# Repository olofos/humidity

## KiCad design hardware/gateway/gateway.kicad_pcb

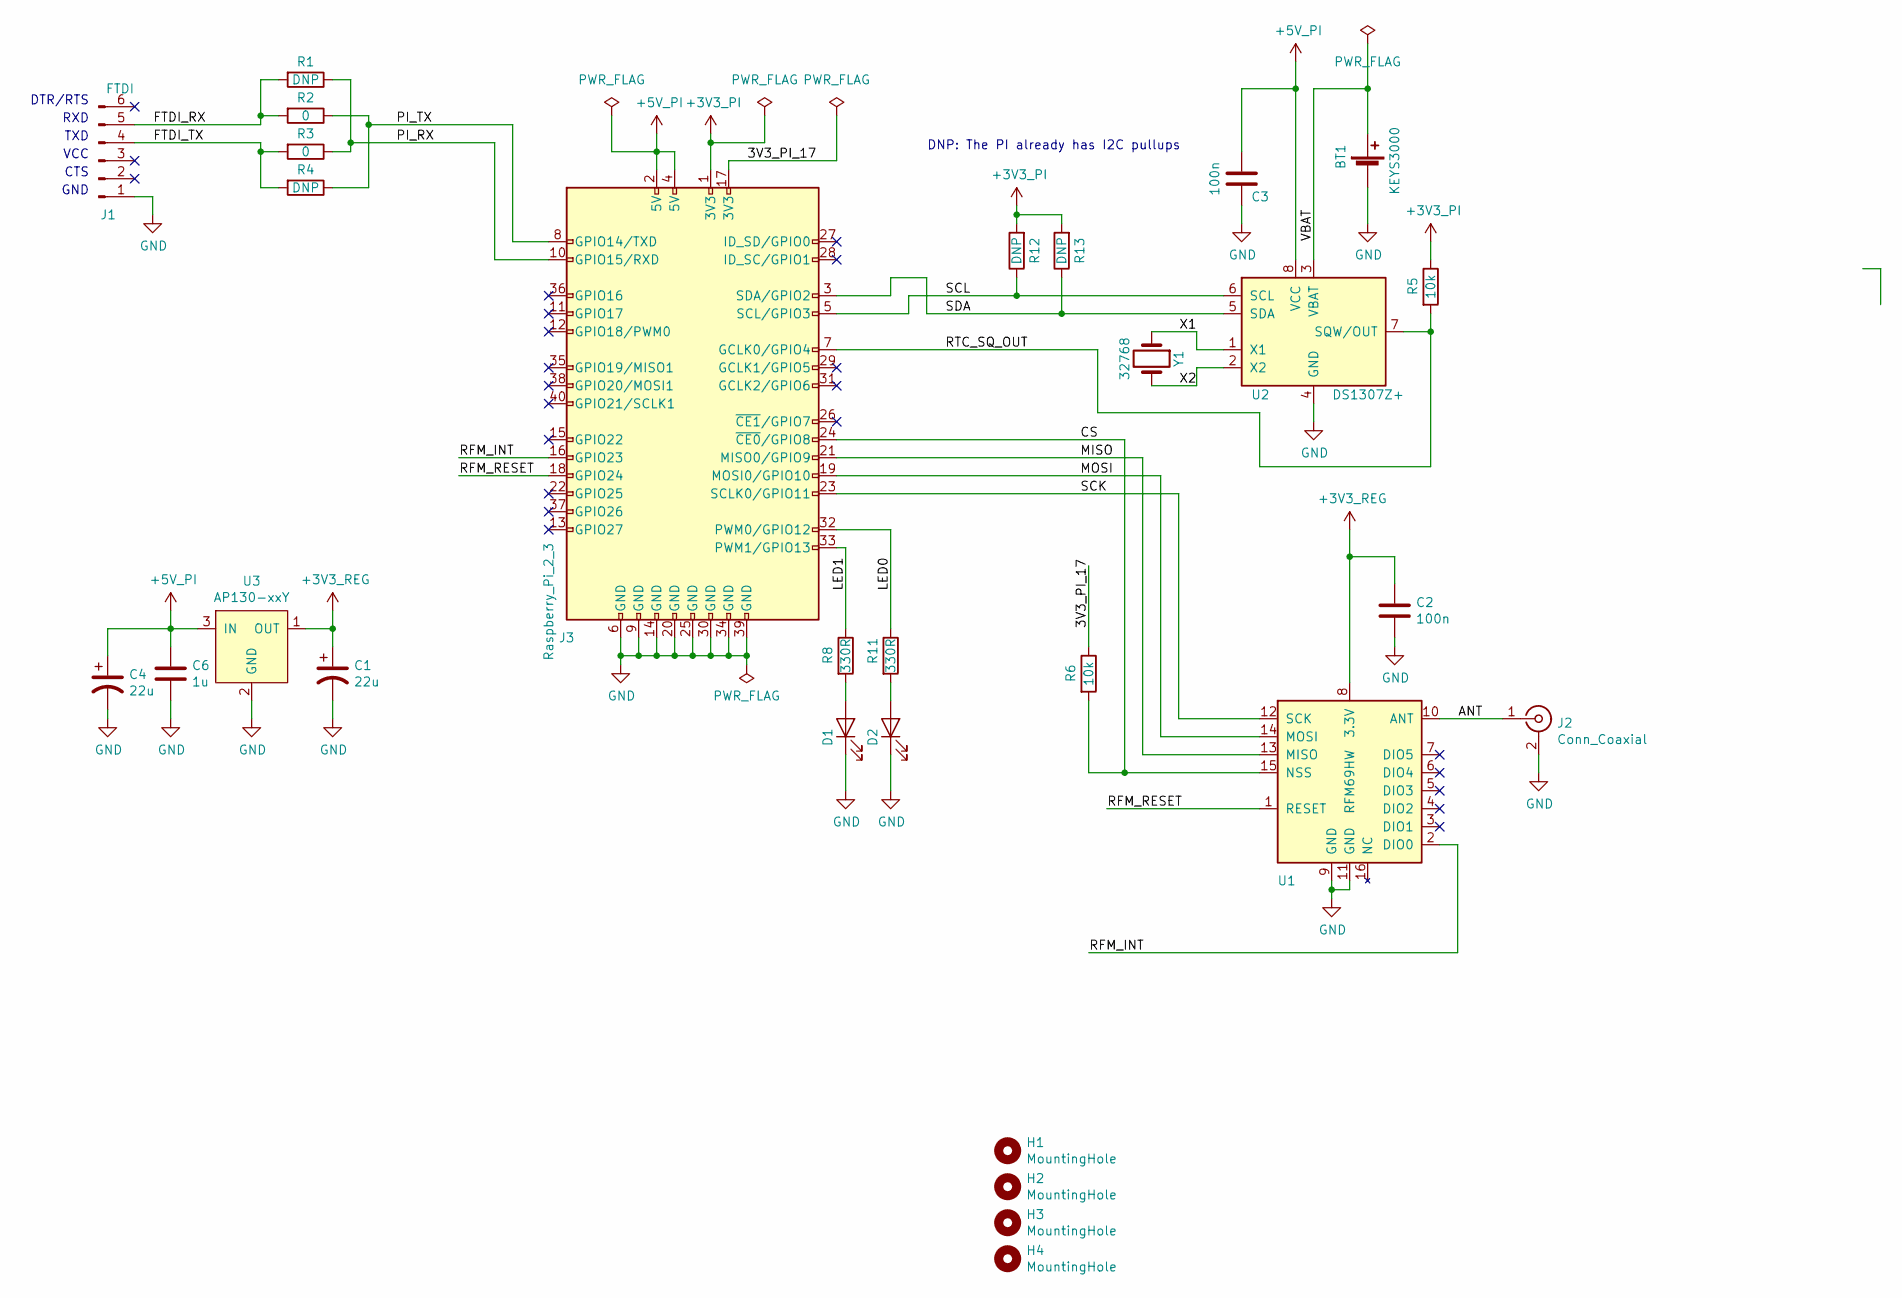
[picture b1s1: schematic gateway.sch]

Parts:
BT1: KEYS3000; CR1216_Keystone_3000
C1, C4: 22u; CP_Elec_5x5.3
C2, C3: 100n; C_0603_1608Metric_Pad1.05x0.95mm_HandSolder
C6: 1u; C_0805_2012Metric_Pad1.15x1.40mm_HandSolder
D1: KP-2012LSURCK; LED_0805_2012Metric_Pad1.15x1.40mm_HandSolder
D2: KP-2012LSGC; LED_0805_2012Metric_Pad1.15x1.40mm_HandSolder
H1, H2, H3, H4: MountingHole; MountingHole_2.7mm_M2.5
J1: FTDI; PinHeader_1x06_P2.54mm_Horizontal
J2: Conn_Coaxial; Adam_Tech_SMA_Female_RF2-19A
J3: Raspberry_Pi_2_3; PinSocket_2x20_P2.54mm_Vertical_SMD
R1, R4, R12, R13: DNP; R_0603_1608Metric_Pad1.05x0.95mm_HandSolder-DNP
R2, R3: 0; R_0603_1608Metric_Pad1.05x0.95mm_HandSolder
R5, R6: 10k; R_0603_1608Metric_Pad1.05x0.95mm_HandSolder
R8, R11: 330R; R_0603_1608Metric_Pad1.05x0.95mm_HandSolder
U1: RFM69HW
U2: DS1307Z+; SOIC-8_3.9x4.9mm_P1.27mm
U3: AP130-xxY; SOT-89-3_Handsoldering
Y1: 32768; Crystal_C26-LF_D2.1mm_L6.5mm_Horizontal

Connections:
+3V3_PI: J3.1 (3V3), R5.1, R12.2, R13.2
+3V3_REG: C1.1, C2.1, U1.8 (3.3V), U3.1 (OUT)
+5V_PI: C3.1, C4.1, C6.1, J3.2 (5V), J3.4 (5V), U2.8 (VCC), U3.3 (IN)
/3V3_PI_17: J3.17 (3V3), R6.1
/ANT: J2.1 (In), U1.10 (ANT)
/CS: J3.24 (~CE0~/GPIO8), R6.2, U1.15 (NSS)
/FTDI_RX: J1.5, R1.2, R2.2
/FTDI_TX: J1.4, R3.2, R4.2
/LED0: J3.32 (PWM0/GPIO12), R11.1
/LED1: J3.33 (PWM1/GPIO13), R8.1
/MISO: J3.21 (MISO0/GPIO9), U1.13 (MISO)
/MOSI: J3.19 (MOSI0/GPIO10), U1.14 (MOSI)
/PI_RX: J3.10 (GPIO15/RXD), R1.1, R3.1
/PI_TX: J3.8 (GPIO14/TXD), R2.1, R4.1
/RFM_INT: J3.16 (GPIO23), U1.2 (DIO0)
/RFM_RESET: J3.18 (GPIO24), U1.1 (RESET)
/RTC_SQ_OUT: J3.7 (GCLK0/GPIO4), R5.2, U2.7 (SQW/OUT)
/SCK: J3.23 (SCLK0/GPIO11), U1.12 (SCK)
/SCL: J3.5 (SCL/GPIO3), R12.1, U2.6 (SCL)
/SDA: J3.3 (SDA/GPIO2), R13.1, U2.5 (SDA)
/VBAT: BT1.1 (+), U2.3 (VBAT)
/X1: U2.1 (X1), Y1.1
/X2: U2.2 (X2), Y1.2
GND: BT1.2 (-), C1.2, C2.2, C3.2, C4.2, C6.2, D1.1 (K), D2.1 (K), J1.1, J2.2 (Ext), J3.6 (GND), J3.9 (GND), J3.14 (GND), J3.20 (GND), J3.25 (GND), J3.30 (GND), J3.34 (GND), J3.39 (GND), U1.9 (GND), U1.11 (GND), U2.4 (GND), U3.2 (GND)
unnamed: D1.2 (A), R8.2
unnamed: D2.2 (A), R11.2

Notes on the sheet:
GND
CTS
VCC
TXD
RXD
DTR/RTS
DNP: The PI already has I2C pullups

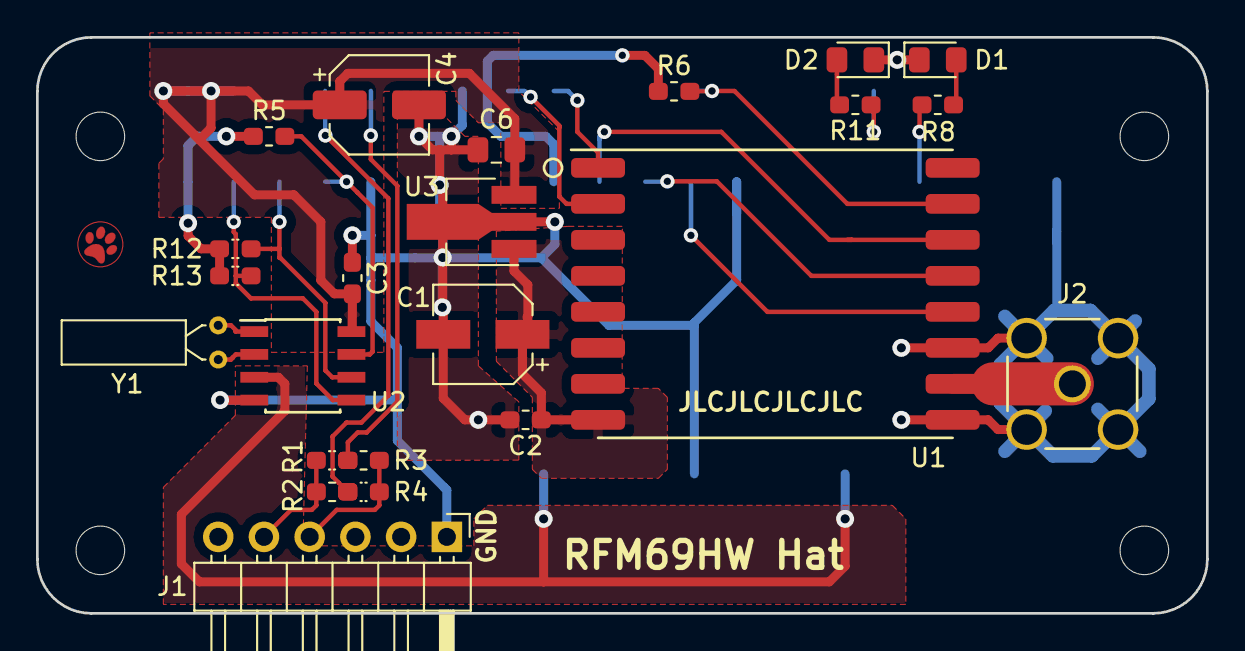
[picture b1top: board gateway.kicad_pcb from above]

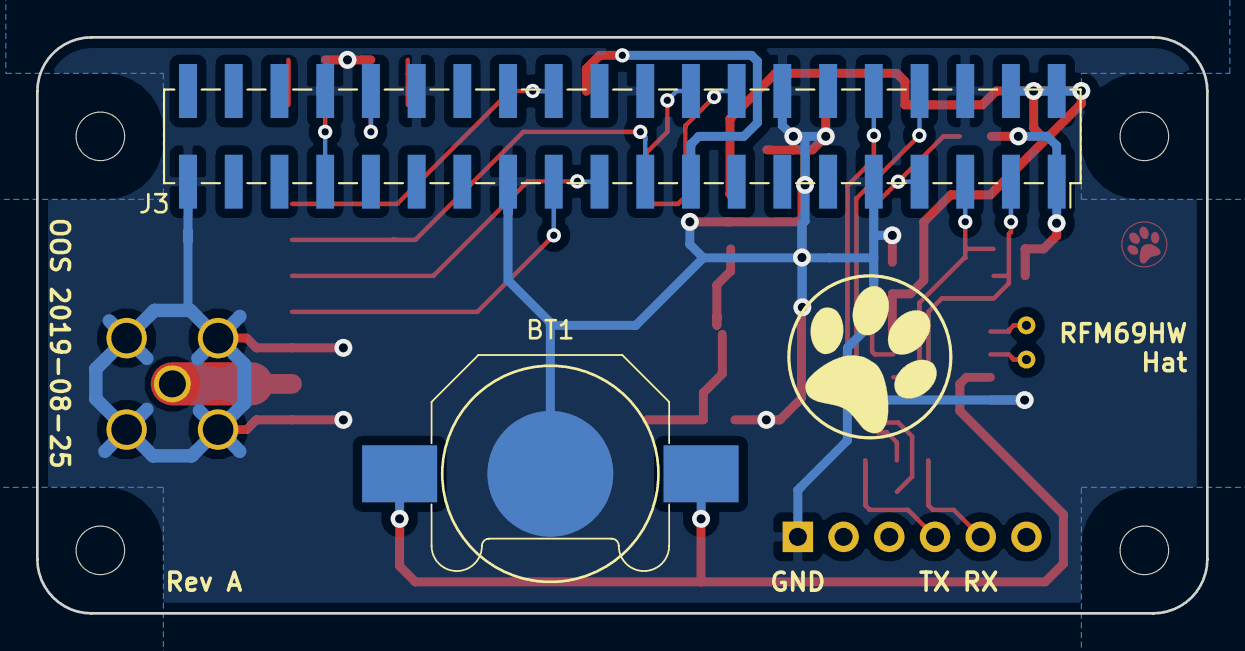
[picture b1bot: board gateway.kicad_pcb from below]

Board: 2 copper layers, 65.0 x 32.0 mm, 29 parts (2 on the bottom side), 26 nets.

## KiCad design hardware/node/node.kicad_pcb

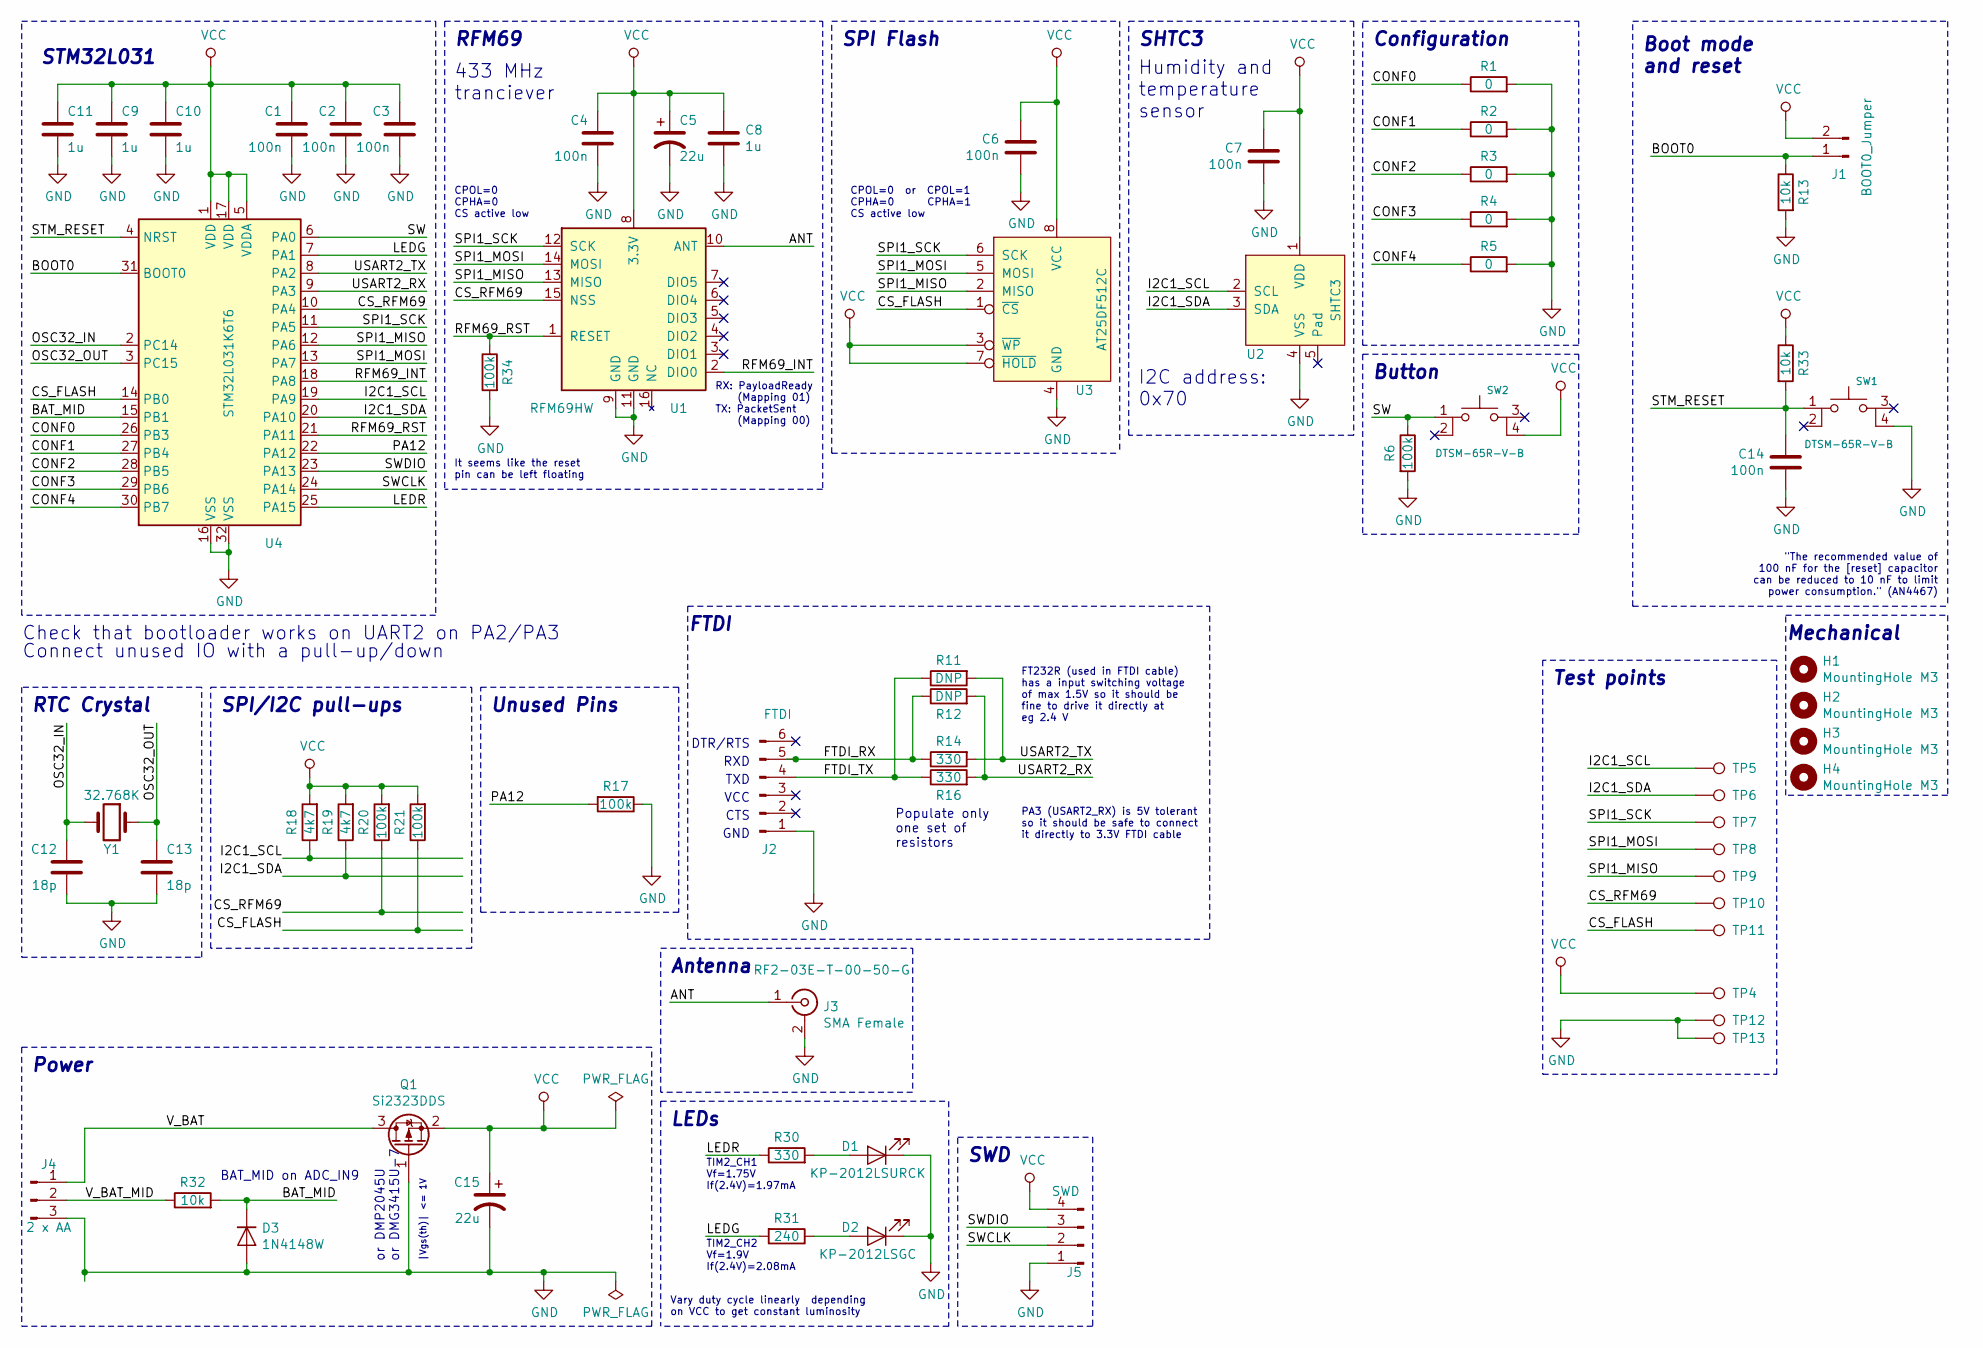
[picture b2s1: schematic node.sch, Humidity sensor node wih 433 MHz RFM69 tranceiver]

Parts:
C1, C2, C3, C4, C6, C7, C14: 100n; C_0603_1608Metric_Pad1.05x0.95mm_HandSolder
C5, C15: 22u; CP_Elec_5x5.3
C8, C9, C10, C11: 1u; C_0805_2012Metric_Pad1.15x1.40mm_HandSolder
C12, C13: 18p; C_0603_1608Metric_Pad1.05x0.95mm_HandSolder
D1: KP-2012LSURCK; LED_0805_2012Metric_Pad1.15x1.40mm_HandSolder
D2: KP-2012LSGC; LED_0805_2012Metric_Pad1.15x1.40mm_HandSolder
D3: 1N4148W; D_SOD-123
H1, H2, H3, H4: MountingHole M3; MountingHole_3.2mm_M3
J1: BOOT0_Jumper; PinHeader_1x02_P2.54mm_Vertical
J2: FTDI; PinHeader_1x06_P2.54mm_Horizontal
J3: SMA Female; Adam_Tech_SMA_Female_RF2-19A; Part RF2-03E-T-00-50-G
J4: 2 x AA; PinHeader_1x03_P2.54mm_Vertical
J5: SWD; PinHeader_1x04_P2.54mm_Horizontal
Q1: Si2323DDS; SOT-23_Handsoldering
R1, R2, R3, R4, R5: 0; R_0603_1608Metric_Pad1.05x0.95mm_HandSolder
R6, R17, R20, R21, R34: 100k; R_0603_1608Metric_Pad1.05x0.95mm_HandSolder
R11, R12: DNP; R_0603_1608Metric_Pad1.05x0.95mm_HandSolder-DNP
R13, R32, R33: 10k; R_0603_1608Metric_Pad1.05x0.95mm_HandSolder
R14, R16, R30: 330; R_0603_1608Metric_Pad1.05x0.95mm_HandSolder
R18, R19: 4k7; R_0603_1608Metric_Pad1.05x0.95mm_HandSolder
R31: 240; R_0603_1608Metric_Pad1.05x0.95mm_HandSolder
SW1, SW2: DTSM-65R-V-B; SW_SPST_DTSM-6
TP4, TP5, TP6, TP7, TP8, TP9, TP10, TP11: TestPoint; TestPoint_THTPad_D1.5mm_Drill0.7mm
TP12, TP13: TestPoint; TestPoint_THTPad_1.5x1.5mm_Drill0.7mm
U1: RFM69HW
U2: SHTC3
U3: AT25DF512C; SOIC-8_3.9x4.9mm_P1.27mm
U4: STM32L031K6T6; LQFP-32_7x7mm_P0.8mm
Y1: 32.768K; Crystal_C26-LF_D2.1mm_L6.5mm_Horizontal

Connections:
/ANT: J3.1 (In), U1.10 (ANT)
/BAT_MID: D3.1 (K), R32.2, U4.15 (PB1)
/BOOT0: J1.1, R13.1, U4.31 (BOOT0)
/CONF0: R1.1, U4.26 (PB3)
/CONF1: R2.1, U4.27 (PB4)
/CONF2: R3.1, U4.28 (PB5)
/CONF3: R4.1, U4.29 (PB6)
/CONF4: R5.1, U4.30 (PB7)
/CS_FLASH: R21.1, TP11.1, U3.1 (~CS), U4.14 (PB0)
/CS_RFM69: R20.1, TP10.1, U1.15 (NSS), U4.10 (PA4)
/FTDI_RX: J2.5, R12.1, R14.1
/FTDI_TX: J2.4, R11.1, R16.1
/I2C1_SCL: R18.1, TP5.1, U2.2 (SCL), U4.19 (PA9)
/I2C1_SDA: R19.1, TP6.1, U2.3 (SDA), U4.20 (PA10)
/LEDG: R31.2, U4.7 (PA1)
/LEDR: R30.1, U4.25 (PA15)
/OSC32_IN: C12.2, U4.2 (PC14), Y1.2
/OSC32_OUT: C13.1, U4.3 (PC15), Y1.1
/PA12: R17.2, U4.22 (PA12)
/RFM69_INT: U1.2 (DIO0), U4.18 (PA8)
/RFM69_RST: R34.1, U1.1 (RESET), U4.21 (PA11)
/SPI1_MISO: TP9.1, U1.13 (MISO), U3.2 (MISO), U4.12 (PA6)
/SPI1_MOSI: TP8.1, U1.14 (MOSI), U3.5 (MOSI), U4.13 (PA7)
/SPI1_SCK: TP7.1, U1.12 (SCK), U3.6 (SCK), U4.11 (PA5)
/STM_RESET: C14.2, R33.2, SW1.1, U4.4 (NRST)
/SW: R6.1, SW2.1, U4.6 (PA0)
/SWCLK: J5.2, U4.24 (PA14)
/SWDIO: J5.3, U4.23 (PA13)
/USART2_RX: R12.2, R16.2, U4.9 (PA3)
/USART2_TX: R11.2, R14.2, U4.8 (PA2)
/V_BAT: J4.1, Q1.3 (D)
/V_BAT_MID: J4.2, R32.1
GND: C1.1, C2.1, C3.1, C4.1, C5.2, C6.1, C7.1, C8.2, C9.2, C10.2, C11.2, C12.1, C13.2, C14.1, C15.2, D1.1 (K), D2.1 (K), D3.2 (A), J2.1, J3.2 (Ext), J4.3, J5.1, Q1.1 (G), R1.2, R2.2, R3.2, R4.2, R5.2, R6.2, R13.2, R17.1, R34.2, SW1.4, TP12.1, TP13.1, U1.9 (GND), U1.11 (GND), U2.4 (VSS), U3.4 (GND), U4.16 (VSS), U4.32 (VSS)
unnamed: D1.2 (A), R30.2
unnamed: D2.2 (A), R31.1
VCC: C1.2, C2.2, C3.2, C4.2, C5.1, C6.2, C7.2, C8.1, C9.1, C10.1, C11.1, C15.1, J1.2, J5.4, Q1.2 (S), R18.2, R19.2, R20.2, R21.2, R33.1, SW2.4, TP4.1, U1.8 (3.3V), U2.1 (VDD), U3.3 (~WP), U3.7 (~HOLD), U3.8 (VCC), U4.1 (VDD), U4.5 (VDDA), U4.17 (VDD)

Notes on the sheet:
GND
CTS
VCC
TXD
RXD
DTR/RTS
Populate only one set of resistors
RTC Crystal
Power
Configuration
SPI/I2C pull-ups
SWD
FTDI
Boot mode and reset
LEDs
SHTC3
Humidity and temperature sensor
I2C address: 0x70
SPI Flash
RFM69
433 MHz tranciever
STM32L031
Check that bootloader works on UART2 on PA2/PA3
Connect unused IO with a pull-up/down
or DMP2045U or DMG3415U-7
|Vgs(th)| <= 1V
RX: PayloadReady (Mapping 01) TX: PacketSent (Mapping 00)
Antenna
Unused Pins
CPOL=0 CPHA=0 CS active low
CPOL=0 or CPOL=1 CPHA=0 CPHA=1 CS active low
TIM2_CH1 Vf=1.75V If(2.4V)=1.97mA
TIM2_CH2 Vf=1.9V If(2.4V)=2.08mA
PA3 (USART2_RX) is 5V tolerant so it should be safe to connect it directly to 3.3V FTDI cable
FT232R (used in FTDI cable) has a input switching voltage of max 1.5V so it should be fine to drive it directly at eg 2.4 V
It seems like the reset pin can be left floating
Vary duty cycle linearly depending on VCC to get constant luminosity
"The recommended value of 100 nF for the [reset] capacitor can be reduced to 10 nF to limit power consumption." (AN4467)
Mechanical
BAT_MID on ADC_IN9

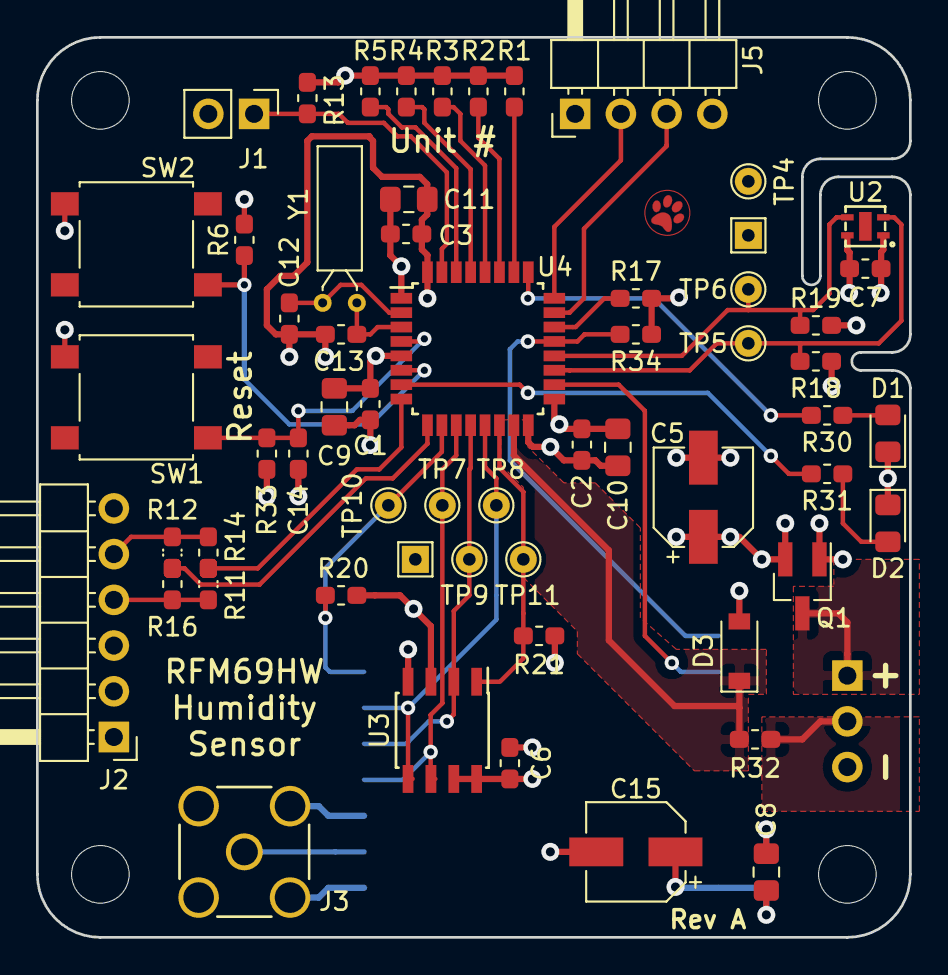
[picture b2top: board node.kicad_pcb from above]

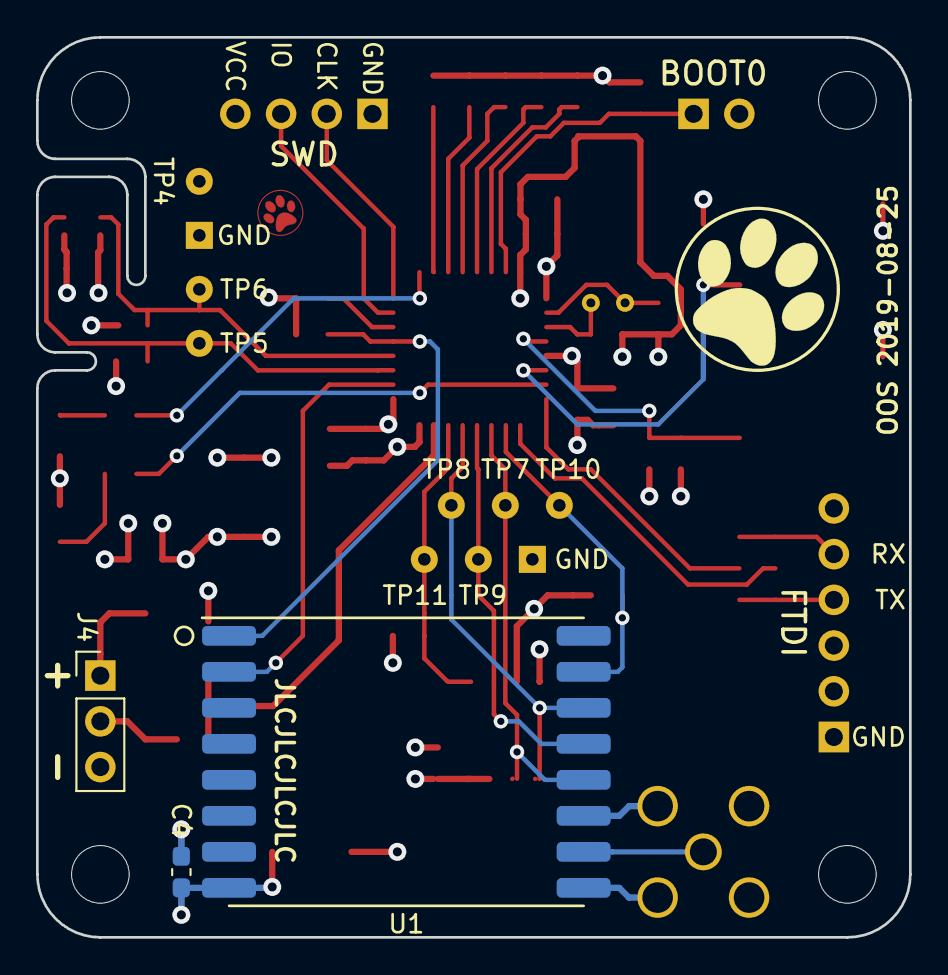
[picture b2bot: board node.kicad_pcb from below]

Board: 4 copper layers, 48.5 x 50.0 mm, 66 parts (3 on the bottom side), 36 nets.

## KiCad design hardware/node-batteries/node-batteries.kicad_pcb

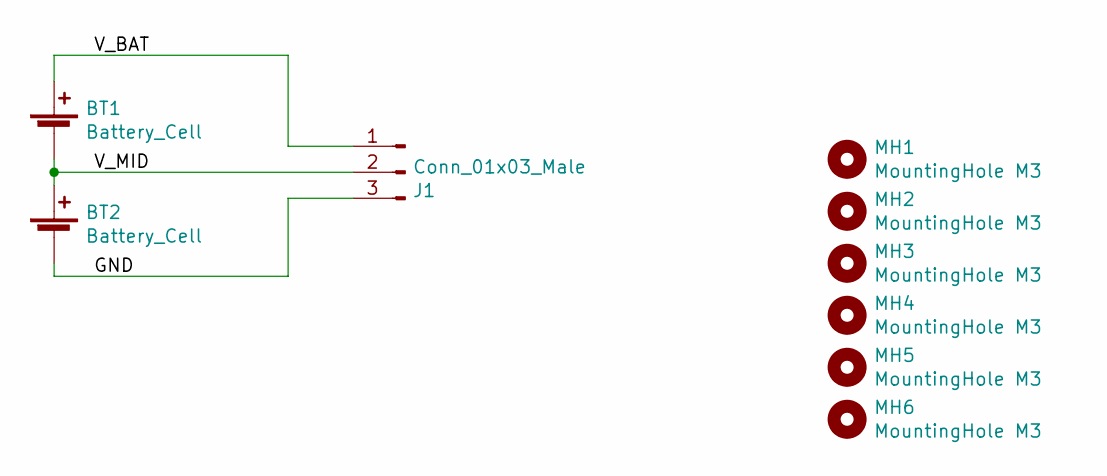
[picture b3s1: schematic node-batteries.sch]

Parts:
BT1, BT2: Battery_Cell; AA_Battery_Holder
J1: Conn_01x03_Male; PinSocket_1x03_P2.54mm_Vertical
MH1, MH2, MH3, MH4, MH5, MH6: MountingHole M3; MountingHole_3.2mm_M3

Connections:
/GND: BT2.2 (-), J1.3
/V_BAT: BT1.1 (+), J1.1
/V_MID: BT1.2 (-), BT2.1 (+), J1.2

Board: 2 copper layers, 9 parts (2 on the bottom side), 3 nets, no tracks yet.

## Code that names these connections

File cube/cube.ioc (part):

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Mcu.Name=STM32L031K(4-6)Tx
Mcu.Package=LQFP32
Mcu.UserName=STM32L031K6Tx
PA0-CK_IN.GPIOParameters=GPIO_Label
PA0-CK_IN.GPIO_Label=TIM2_CH1_LED0
PA0-CK_IN.Signal=S_TIM2_CH1
PA1.GPIOParameters=GPIO_Label
PA1.GPIO_Label=TIM2_CH2_LED1
PA1.Signal=S_TIM2_CH2
PA10.Mode=I2C
PA10.Signal=I2C1_SDA
PA13.Mode=Serial_Wire
PA13.Signal=SYS_SWDIO
PA14.Mode=Serial_Wire
PA14.Signal=SYS_SWCLK
PA2.Signal=LPUART1_TX
PA3.Signal=LPUART1_RX
PA4.Mode=IN4
PA4.Signal=ADC_IN4
PA5.Mode=Full_Duplex_Master
PA5.Signal=SPI1_SCK
PA6.Mode=Full_Duplex_Master
PA6.Signal=SPI1_MISO
PA7.Mode=Full_Duplex_Master
PA7.Signal=SPI1_MOSI
PA8.GPIOParameters=GPIO_Label
PA8.GPIO_Label=RFM69_INT
PA8.Signal=GPIO_Input
PA9.Mode=I2C
PA9.Signal=I2C1_SCL
PB0.GPIOParameters=GPIO_Label
PB0.GPIO_Label=SPI_CS_RFM69
PB0.Signal=GPIO_Output
PB1.GPIOParameters=GPIO_Label
PB1.GPIO_Label=SPI_CS_FLASH
PB1.Signal=GPIO_Output
PB3.GPIOParameters=GPIO_PuPd,GPIO_Label
PB3.GPIO_Label=CONF0
PB3.GPIO_PuPd=GPIO_PULLUP
PB3.Signal=GPIO_Input
PB4.GPIOParameters=GPIO_PuPd,GPIO_Label
PB4.GPIO_Label=CONF1
PB4.GPIO_PuPd=GPIO_PULLUP
PB4.Signal=GPIO_Input
PB5.GPIOParameters=GPIO_PuPd,GPIO_Label
PB5.GPIO_Label=CONF2
PB5.GPIO_PuPd=GPIO_PULLUP
PB5.Signal=GPIO_Input
PB6.GPIOParameters=GPIO_PuPd,GPIO_Label
PB6.GPIO_Label=CONF3
PB6.GPIO_PuPd=GPIO_PULLUP
PB6.Signal=GPIO_Input
PB7.GPIOParameters=GPIO_PuPd,GPIO_Label
PB7.GPIO_Label=CONF4
PB7.GPIO_PuPd=GPIO_PULLUP
PB7.Signal=GPIO_Input
PC14-OSC32_IN.Mode=LSE-External-Oscillator
PC14-OSC32_IN.Signal=RCC_OSC32_IN
PC15-OSC32_OUT.Mode=LSE-External-Oscillator
PC15-OSC32_OUT.Signal=RCC_OSC32_OUT
RCC.HSE_VALUE=8000000
RCC.SYSCLKFreq_VALUE=2097000
board=custom

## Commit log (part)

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2019-05-23 Initial commit with some basic design documents
2019-05-23 Initial node schematic
2019-05-23 Removed UART level translation
2019-05-23 Added 4 x M3 mounting holes
2019-05-23 PCB mount battery holders
2019-05-25 First layout
2019-05-25 PCB with batteries
2019-05-25 PCB with batteries on JST PH
2019-05-26 Battery connector on the other side
2019-05-27 Connect RFM69 reset to STM32
2019-05-28 Change to RFM69HW
2019-05-28 Added RFM69W step model
2019-06-03 Added 3d models
2019-06-03 Added battery holder PCB
2019-06-03 Moved mounting holes. Slightly narrower PCB
2019-06-03 Move power connector to other side
2019-06-03 Adjust mounting holes
2019-06-03 Add resistors as DNP
2019-06-03 Use only resistors to ground to config unit #
2019-06-03 Added missing file
2019-06-07 Changed switch
2019-06-07 Added mounting tabs to battery PCB
2019-06-07 Basic gateway schematic
2019-06-11 Gateway schematic
2019-06-13 Gateway PCB
2019-06-13 Added .gitignore
2019-06-13 Added missing cache file
2019-06-13 Added part numbers to node schematic
2019-06-13 Added part numbers to node-batteries
2019-06-13 Started making a BOM
2019-06-13 Made paths to 3d models relative
2019-06-13 Updated .gitignore
2019-06-13 Added some silkscreen
2019-06-15 Added local 3V3 regulator
2019-06-15 Changed to 22u bul caps
2019-06-18 Layout improvemnets
2019-06-20 Improved mounting holes and planes
2019-06-23 Improved optional resistors
2019-06-24 DS1307 and PTH crystal
2019-06-24 Minor layout adjustments
2019-06-27 Slight layout adjustments
2019-06-27 Added extra decoupling
2019-06-27 Shortened SPI traces
2019-06-27 Further cleanup of node PCB
2019-06-27 Added extra input cap and CS pullup to gateway
2019-06-27 Improved GND
2019-08-07 Added an extra push button for user input
2019-08-07 Cleaned up schematic
2019-08-07 Small udjustments to gateway PCB
2019-08-07 Adjusted silk screen
2019-08-10 Exchanged pins LEDR (PA0) <-> SW (PA15)
    LEDR is still on TIM2_CH1
    SW is now on WKUP1 and can hence be used to exit the mcu from standby
2019-08-11 Removed TODO
2019-08-11 Added pulldown to switch
2019-08-25 Updated date
2019-08-25 Add silkscreen for JLCPCB order number
2019-09-09 Basic software framework for node
2019-09-09 Start mcu bringup
2019-09-09 Systick timer
2019-09-10 LPUART
2019-09-11 Move GPIO defines to separate file
2019-09-11 Added basic SPI driver
2019-09-11 Use spi_read and spi_write instead of spi_transfer
2019-09-11 Properly wait before disabling SPI
2019-09-11 Basic SPI Flash API
2019-09-12 Deassert CS pin when done
2019-09-12 spi_read -> spi_read_byte, spi_write -> spi_write_byte
2019-09-15 Added basic UART API
2019-09-24 Basic I2C driver
2019-09-24 Added systick API
2019-09-24 Added missing prototype
2019-09-24 Added timeout to I2C API
2019-09-24 Added SHTC3 API
2019-09-24 Add spi_read and spi_write to read/write multiple bytes
2019-09-24 Use spi_read/spi_write for SPI flash
2019-09-24 Add new files to Makefile
2019-09-24 Check SHTC3 CRC
2019-09-25 Added optional table implementation of CRC
2019-09-25 Basic ADC API
2019-09-26 Clean up SPI driver flag waiting
2019-09-26 Added tests for SPI driver
2019-09-26 SPI driver now passes tests
2019-09-27 Write and read each byte separately in SPI driver
    We wait for RXNE after each byte. This is slower since we are not
    sending the next byte as soon as TXE is set. However, we make sure to
    not miss any bytes by being to slow, which could make us stuck at a
    busy loop. This ensures we are not failing if we receive an interrupt
    somewhere during the transfer, and allows us to use a higher clock frequency.
2019-09-27 Introduce named constants for SPI baud rate divider
2019-09-27 SPI flash ultra deep sleep and wakeup
2019-09-27 Add comment
2019-10-05 Add MODER_MASK constant
2019-10-05 Basic RFM69 API
    Based on Adafruit's circuitpython driver
2019-10-05 Fix test deps directory
2019-10-05 Ignore .deps
2019-10-06 Simplify RFM69 HAL level
2019-10-07 Rename rfm69_(read|write) -> rfm69_hal_(read|write)
2019-10-07 Change rfm69_send/rfm69_receive to rfm69_write/rfm69_read
2019-10-07 Remove debug printf
2019-10-07 Added rfm69_get_rssi
2019-10-07 Return proper error codes
2019-10-10 Add RFM69 HAL init/deinit
2019-10-10 Added missing prototypes
2019-10-10 Change and document rfm69_wait_for_* return values
2019-10-10 Add node address filtering
2019-10-10 Automatically send own address after length and target address
2019-10-10 Make spi_write buffer const
2019-10-10 Make rfm69_hal_write buffer const
2019-10-10 Support RFM69 AES encryption
2019-10-10 Make i2c_register_write buf const
2019-10-10 Use RFM69 interrupt pin
2019-10-10 Added rfm69_test
2019-10-10 Added spi_flash_test
2019-10-10 Started adding RTC API
2019-10-10 Added missing file to Makefile
2019-10-10 Generate checksum during build
2019-10-10 Add checksum section to linker script
2019-10-12 Added rtc_set_periodic_wakeup
2019-10-12 Add systick_(pause|resume)
2019-10-12 shtc3_read takes a struct shtc3_measurement*
2019-10-12 adc_measure_voltages can fail with a timeout
2019-10-12 Correct temperature format
2019-10-12 Add rtc_wait_for_lse
2019-10-12 Rename supply_voltages to adc_supply_voltages
2019-10-12 Rename structure in c file as well
2019-10-14 Add timeout to ADC
2019-10-14 Correct temperature bit shift
2019-10-16 Make buf parameter of rfm69_write const
2019-10-16 Basic working main for node
2019-10-16 RFM69 HAL for Raspberry Pi
2019-10-16 Database API
2019-10-16 Add SQLITE3 amalgamation version 3.30.1
2019-10-16 Add PI main
2019-10-16 Add basic Makefile for pi
2019-10-16 Added circular buffer in SPI Flash
2019-10-17 Make reading and increasing tail separate steps in SPI flash cbuf
2019-10-21 Add bootloader section
2019-10-28 Set ADC sampling time
2019-10-28 Correct pin name
2019-10-29 Remove rtc_are_peripherals_initialized
    Check PWR->CSR & PWR_CSR_SBF instead to find out if we are waking up
    from standby or starting from scratch
2019-10-29 Move checksum out of RTC driver
2019-10-29 Factor out pretty printing functions
2019-10-29 Allow uart_*_init to be reetrant
2019-10-29 Clear flags wakeup on reset
2019-10-29 NACK with NOT_REGISTERED if node not found
2019-10-29 Don't accept measurements that are too old
2019-10-29 Introduce separate state for sending measurement
2019-10-29 Restrore deleted functions
2019-11-03 Loop with blinking on error at startup
2019-11-03 Use stop mode after failure when sending measurement
2020-07-05 Add cbuf_peek
2020-07-05 Update RFM69 config
2020-07-05 Keep track of next measurement
2020-07-05 Always put RFM69 to sleep
2020-07-05 Pull out magic string
2020-07-05 Save measurement to a cbuf instead of flash
2020-07-05 Update db path
2020-07-05 Print RSSI
2020-07-05 Improved message
2020-07-05 Support debug packages
2020-07-05 Updated database schema
2020-07-05 Add pkg_read_string
2020-07-05 Define constants for sleep periods
2020-07-28 Functions for LED on/off
2020-07-28 Add target to dump lss
2020-07-28 Remove magic constants in UART driver
2020-07-28 Avoid double reads/writes to register
2020-07-28 Improve comments
2020-07-29 Move common source files to separate directory
2020-08-25 Add db support for transactions
    Currently only used in external tests
2020-08-25 Show row id of latest measurement
2020-08-25 Support DB path from environment variable DB
2020-08-25 Nicer printout of measurements
2020-08-25 Clean up Makefile
2020-08-25 Add some comments
2020-08-25 Blink once when running each state handler
2020-08-25 Do a measurement every ten minutes, and adjust other delays
2020-08-25 Send ACK on repeated measurement
2020-08-25 Protect gateway software by filelock
2020-08-27 Signal repeated measurement by returning row_id zero
2020-08-28 Fill binary image with 0xFF between sections
2020-08-29 Correctly print voltage with two decimal places
2020-08-29 Added JLINK scripts for flashing and dumping flash
2020-08-30 Updated BOM
2020-08-30 Add makefile target for flashing node
2020-08-30 Update STM32 cube settings
2020-08-30 Update dev documentation
2020-08-30 Fix typo
2020-08-30 Increase number of saved measurements
2020-08-30 Remove oldest measurement if circular buffer is full
2020-08-31 Removed magic numbers
2020-08-31 Make some functions static
2020-08-31 Introduce cbuf_skip to pop without reading value
2020-08-31 Rename pkg_read -> pkg_receive and pkg_write -> pkg_send
2020-08-31 Document current package structure
2020-08-31 Max package length (with AES) is 48 bytes
2020-08-31 Remove unused code
2020-09-01 Factored out gateway package handling to a separate file
2020-09-01 Don't send empty packages
2020-09-01 Remove some repetition
2020-09-01 Name a magic number
2020-09-01 Move pkg_send from handle_package to main
2020-09-01 Use correct printf format for uint64_t
2020-09-01 Further packet documentation
2020-09-03 Renamed node parameter to node_id
2020-09-03 Remove unused headers
2020-09-03 Use sigaction instead of signal so that syscalls are not restarted
2020-09-03 Specify mode when opening lock file
2020-09-03 Drop top bit of checksum
2020-09-06 echo "\n" is not consistent between shells
2020-09-08 Started implementing next version protocol
2020-09-08 Keep track of seen nodes in memory in addition to in DB
2020-09-08 Refactored package handling
    Preparing for version 1
2020-09-08 Tests for node.c
2020-09-08 CRC32 calculation
2020-09-08 Basic handling of firmware files
2020-09-08 Added mock RFM64 HAL using unix sockets
2020-09-08 Add firmware directory on startup
2020-09-08 Build test server using mocked RFM69
2020-09-08 Simple program to register new firmware
2020-09-08 More documentation
2020-09-08 Build binary image of node firmware by default
2020-09-08 Fix .gitignore
2020-09-08 More tests for handle_package
2020-09-08 Only close what we have opened in RFM69
2020-09-08 Allow any handler to call node_get in tests
2020-09-08 Set RFM69 to sleep mode if sending fails
2020-09-08 Add PKG_FLAG_NO_RETRY
2020-09-08 Require reregistration for unknown nodes
2020-09-08 Added firmware_file_exists
2020-09-08 Check if firmware images exist
2020-09-08 Fix hash strings
2020-09-08 Add crc32.c to Makefile
2020-09-10 Document planned v1 protocol
2020-09-10 Rename environment variable to HUMIDITY_FW
2020-09-10 Added log about clock drift
2020-09-10 Initialise latest_fw_hash to avoid warning from gcc
2020-09-10 Added send_nack function
2020-09-10 Better variable names
2020-09-10 Check that node is properly registered
2020-09-10 Directly use magic numbers in tests
    This ensures that tests fail if the constants are changed by mistake
2020-09-11 Rename FW_UNCHANGED to FW_NO_CHANGE
2020-09-11 Basic gateway support for updates
2020-09-13 Test that cbuf is empty after cbuf_init
2020-09-13 Started implementing new node package handling
2020-09-13 Added test for handle_package
2020-09-13 Added construct_registration_package
2020-09-16 Added construct_(debug|update_request)_package
2020-09-16 Make rtc_(get|set)_time take a pointer to the timestamp
2020-09-16 Added handle_ack_or_nack
2020-09-16 Added more tests and caught a bug in handle_ack_or_nack
2020-09-16 Make construct_debug_package take string length as argument
2020-09-17 Fix typos
2020-09-17 Replace rtc_timestamp with pkg_timestamp
2020-09-17 Let measurement_get return a pointer
2020-09-17 Add cbuf_push_inline
2020-09-18 Check that length of cbuf is power of two
2020-09-18 More static asserts in cbuf_init
2020-09-19 Introduce better cbuf inline API
2020-09-19 Added simple debug interface
2020-09-19 Make construct_registration_package take a debug_message
2020-09-26 Mover crc32.[ch] to common
2020-09-26 Create firmware "hash" from version info + crc32
2020-09-30 Make SPI flash cbuf base address configurable
2020-10-01 Make state global everywhere
2020-10-01 Move MCU setup to separate file
2020-10-01 Use BKP3 for SPI flash
2020-10-01 Add file to take care of update state
2020-10-01 Add new file to Makefile
2020-10-01 Remove duplicate declaration
2020-10-01 Start putting new main file together
2020-10-01 Remove test deps on clean
2021-01-11 Set registered flag on ACK
2021-01-11 Increase node timeout
2021-01-11 Add git version info to node and gateway
2021-01-11 Add optional package debug output
2021-01-23 Added git-version.h and aes-key.h to .gitignore
2021-02-05 Added missing system include file
